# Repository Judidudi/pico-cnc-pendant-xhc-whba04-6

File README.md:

# Universal CNC Pendant

This repository contains the software and hardware for a complete CNC pendant that emulates the USB protocol of the original XHC WHB04B-6 pendant. It is designed to work with LinuxCNC, Beamicon2, Mach3 and Mach4 without any driver changes.

## Features

- **Drop-in WHB04B-6 emulation** – recognized by LinuxCNC's stock `xhc-whb04b-6` driver
- **60 mm handwheel**, rotary switches for axis selection and feed override
- **8 mechanical keys** (Kailh Choc V2) with configurable mapping
- **2.8" TFT touch display** (LVGL) showing machine position and status
- **Hardwired E-stop** – routed as a physical contact to the machine, completely independent of USB
- **Connection watchdog** – the pendant detects a lost host connection and can trigger the E-stop

## Compatibility

| Controller | Status |
|------------|--------|
| LinuxCNC   | To be tested |
| Beamicon2  | WIP |
| Mach3      | WIP |
| Mach4      | WIP |

## Repository structure

```
firmware/        Pico 2 W firmware (C, Pico SDK, TinyUSB, LVGL)
hardware/
  ├─ pcb/        KiCad projects (work in progress)
  ├─ enclosure/  Link to the printable parts on Printables
  └─ bom/        Bill of materials
docs/            Assembly guide, wiring, images
```

## Quickstart

1. Download the latest `.uf2` file from the [Releases](../../releases) page.
2. Hold the **BOOTSEL** button on the Pico while plugging in the USB cable. The Pico shows up as a USB drive.
3. Copy the `.uf2` file onto the drive. The Pico restarts automatically and the pendant is ready to use.

## Safety

- The **RESET** key toggles the machine on/off – it is **not** an emergency stop.
- The pendant's E-stop only protects you if it is wired into your machine's **hardware safety chain**. Never rely on a software-only E-stop.
- This is a hobby project. Build and use it at your own risk.

## To do

- Test and optimize the default button layout and add symbols to the keycaps
- Test with Beamicon2, Mach3 and Mach4
- Finish the hardware watchdog
- Design a custom PCB with an integrated RP2350 and all peripherals

## License

The original work in this repository is licensed under **TODO**, see [LICENSE](LICENSE).

Third-party components keep their own licenses:

| Component | License |
|-----------|---------|
| [LVGL](https://github.com/lvgl/lvgl) v8.3 | MIT |
| [TinyUSB](https://github.com/hathach/tinyusb) (via Pico SDK) | MIT |
| [Raspberry Pi Pico SDK](https://github.com/raspberrypi/pico-sdk) | BSD-3-Clause |

Full license texts: [THIRD_PARTY_LICENSES.md](THIRD_PARTY_LICENSES.md)

## Acknowledgements

- The LinuxCNC project and the authors of the `xhc-whb04b-6` component
- The LVGL and TinyUSB communities

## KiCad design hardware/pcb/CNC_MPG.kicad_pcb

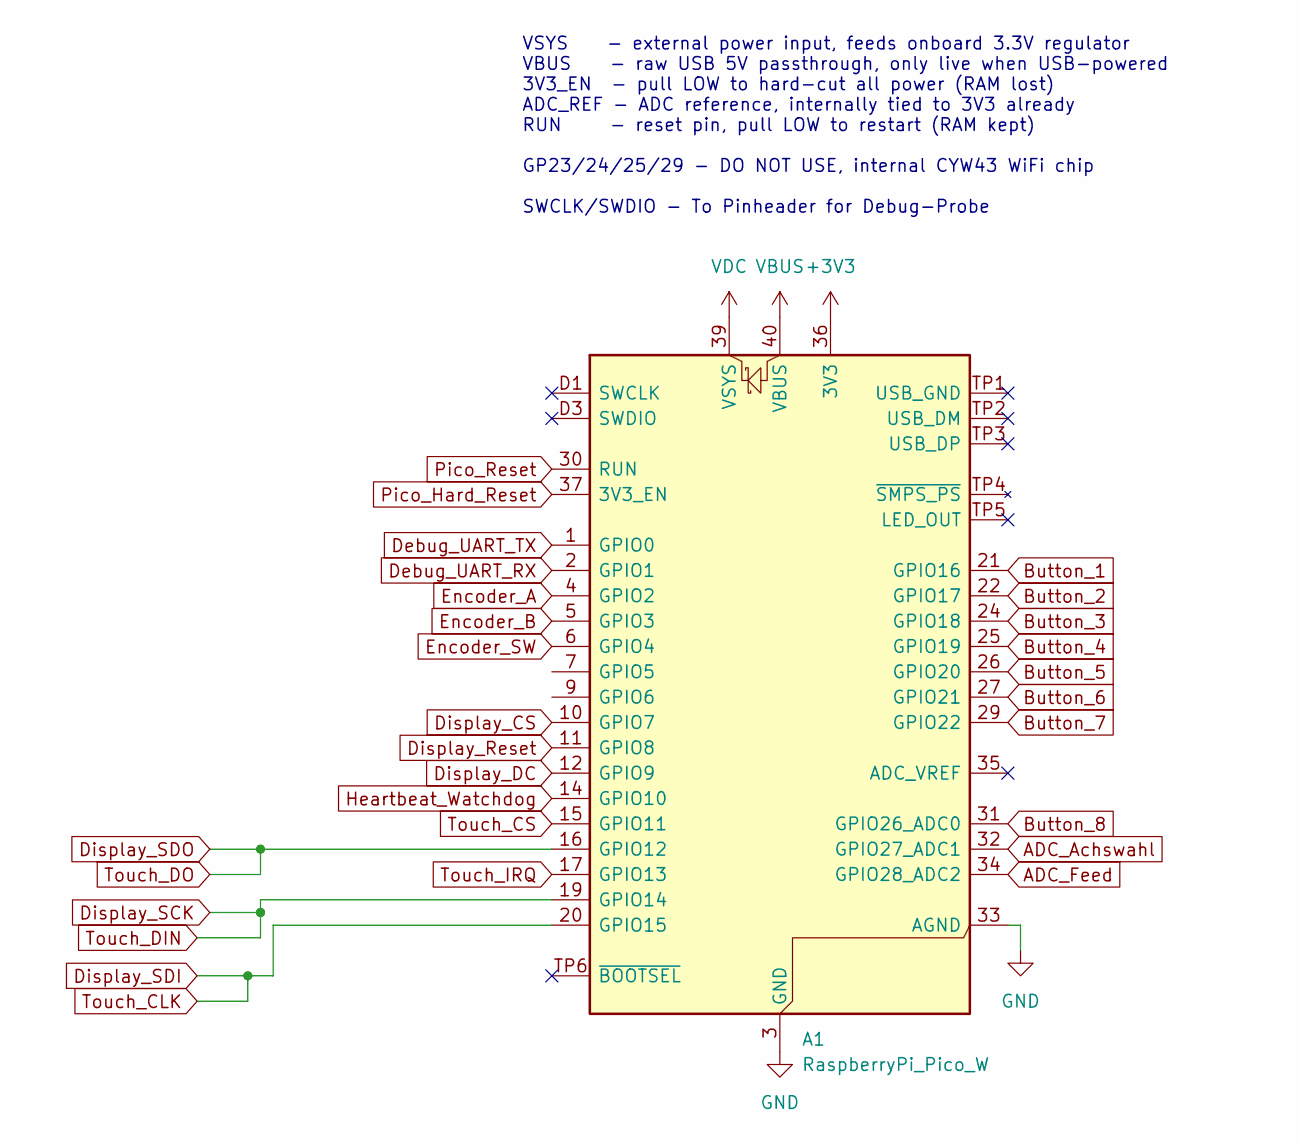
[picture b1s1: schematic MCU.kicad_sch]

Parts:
A1: RaspberryPi_Pico_W; RaspberryPi_Pico_Common_THT

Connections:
ADC_Achswahl: A1.32 (GPIO27_ADC1); also elsewhere on the board
ADC_Feed: A1.34 (GPIO28_ADC2); also elsewhere on the board
Button_1: A1.21 (GPIO16); also elsewhere on the board
Button_2: A1.22 (GPIO17); also elsewhere on the board
Button_3: A1.24 (GPIO18); also elsewhere on the board
Button_4: A1.25 (GPIO19); also elsewhere on the board
Button_5: A1.26 (GPIO20); also elsewhere on the board
Button_6: A1.27 (GPIO21); also elsewhere on the board
Button_7: A1.29 (GPIO22); also elsewhere on the board
Button_8: A1.31 (GPIO26_ADC0); also elsewhere on the board
Debug_UART_RX: A1.2 (GPIO1); also elsewhere on the board
Debug_UART_TX: A1.1 (GPIO0); also elsewhere on the board
Display_CS: A1.10 (GPIO7); also elsewhere on the board
Display_DC: A1.12 (GPIO9); also elsewhere on the board
Display_LED: A1.36 (3V3); also elsewhere on the board
Display_Reset: A1.11 (GPIO8); also elsewhere on the board
Display_SCK: A1.19 (GPIO14); also elsewhere on the board
Display_SDI: A1.20 (GPIO15); also elsewhere on the board
Display_SDO: A1.16 (GPIO12); also elsewhere on the board
Encoder_A: A1.4 (GPIO2); also elsewhere on the board
Encoder_B: A1.5 (GPIO3); also elsewhere on the board
Encoder_SW: A1.6 (GPIO4); also elsewhere on the board
GND: A1.3 (GND), A1.8 (GND), A1.13 (GND), A1.18 (GND), A1.23 (GND), A1.28 (GND), A1.33 (AGND), A1.38 (GND), A1.D2 (GND); also elsewhere on the board
Heartbeat_Watchdog: A1.14 (GPIO10)
Pico_Hard_Reset: A1.37 (3V3_EN)
Pico_Reset: A1.30 (RUN)
Touch_CS: A1.15 (GPIO11); also elsewhere on the board
Touch_IRQ: A1.17 (GPIO13); also elsewhere on the board
VBUS: A1.40 (VBUS)
VDC: A1.39 (VSYS)

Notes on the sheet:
VSYS - external power input, feeds onboard 3.3V regulator VBUS - raw USB 5V passthrough, only live when USB-powered 3V3_EN - pull LOW to hard-cut all power (RAM lost) ADC_REF - ADC reference, internally tied to 3V3 already RUN - reset pin, pull LOW to restart (RAM kept) GP23/24/25/29 - DO NOT USE, 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

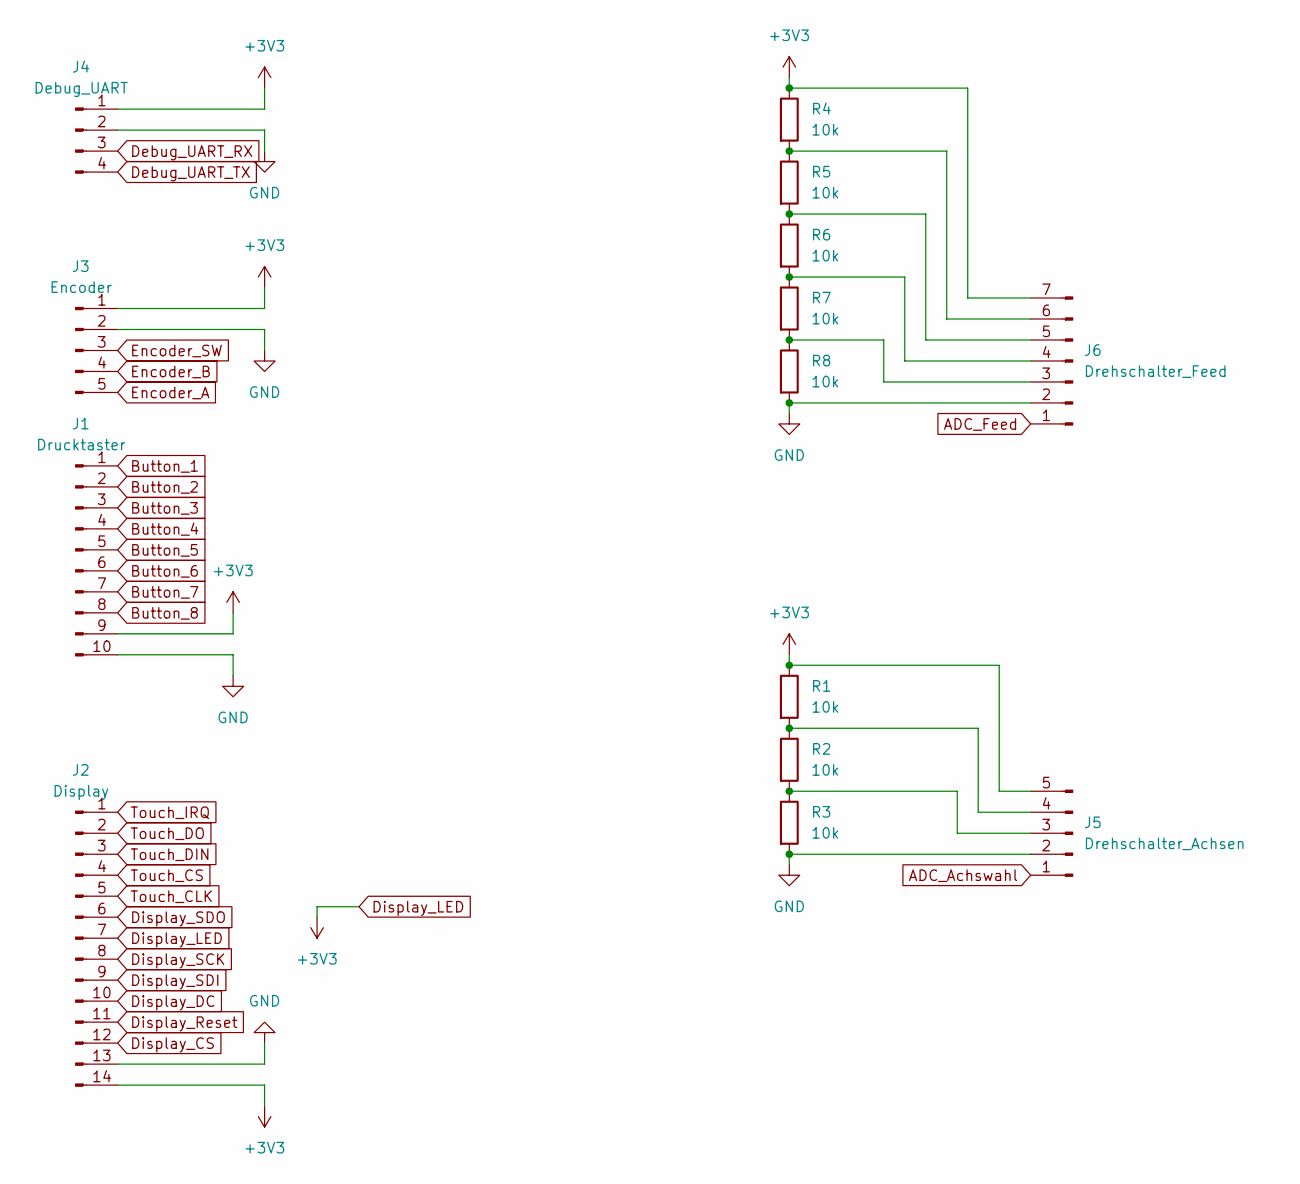
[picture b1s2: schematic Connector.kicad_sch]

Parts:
J1: Drucktaster; JST_PH_B10B-PH-K_1x10_P2.00mm_Vertical
J2: Display; JST_PH_B14B-PH-K_1x14_P2.00mm_Vertical
J3: Encoder; JST_PH_B5B-PH-K_1x05_P2.00mm_Vertical
J4: Debug_UART; PinHeader_1x04_P2.54mm_Vertical
J5: Drehschalter_Achsen; JST_PH_B5B-PH-K_1x05_P2.00mm_Vertical
J6: Drehschalter_Feed; JST_PH_B7B-PH-K_1x07_P2.00mm_Vertical
R1, R2, R3, R4, R5, R6, R7, R8: 10k; R_0603_1608Metric

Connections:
ADC_Achswahl: J5.1; also elsewhere on the board
ADC_Feed: J6.1; also elsewhere on the board
Button_1: J1.1; also elsewhere on the board
Button_2: J1.2; also elsewhere on the board
Button_3: J1.3; also elsewhere on the board
Button_4: J1.4; also elsewhere on the board
Button_5: J1.5; also elsewhere on the board
Button_6: J1.6; also elsewhere on the board
Button_7: J1.7; also elsewhere on the board
Button_8: J1.8; also elsewhere on the board
Debug_UART_RX: J4.3; also elsewhere on the board
Debug_UART_TX: J4.4; also elsewhere on the board
Display_CS: J2.12; also elsewhere on the board
Display_DC: J2.10; also elsewhere on the board
Display_LED: J1.9, J2.7, J2.14, J3.1, J4.1, J5.5, J6.7, R1.1, R4.1; also elsewhere on the board
Display_Reset: J2.11; also elsewhere on the board
Display_SCK: J2.3, J2.8; also elsewhere on the board
Display_SDI: J2.5, J2.9; also elsewhere on the board
Display_SDO: J2.2, J2.6; also elsewhere on the board
Encoder_A: J3.5; also elsewhere on the board
Encoder_B: J3.4; also elsewhere on the board
Encoder_SW: J3.3; also elsewhere on the board
GND: J1.10, J2.13, J3.2, J4.2, J5.2, J6.2, R3.2, R8.2; also elsewhere on the board
unnamed: J5.3, R2.2, R3.1
unnamed: J5.4, R1.2, R2.1
unnamed: J6.3, R7.2, R8.1
unnamed: J6.4, R6.2, R7.1
unnamed: J6.5, R5.2, R6.1
unnamed: J6.6, R4.2, R5.1
Touch_CS: J2.4; also elsewhere on the board
Touch_IRQ: J2.1; also elsewhere on the board

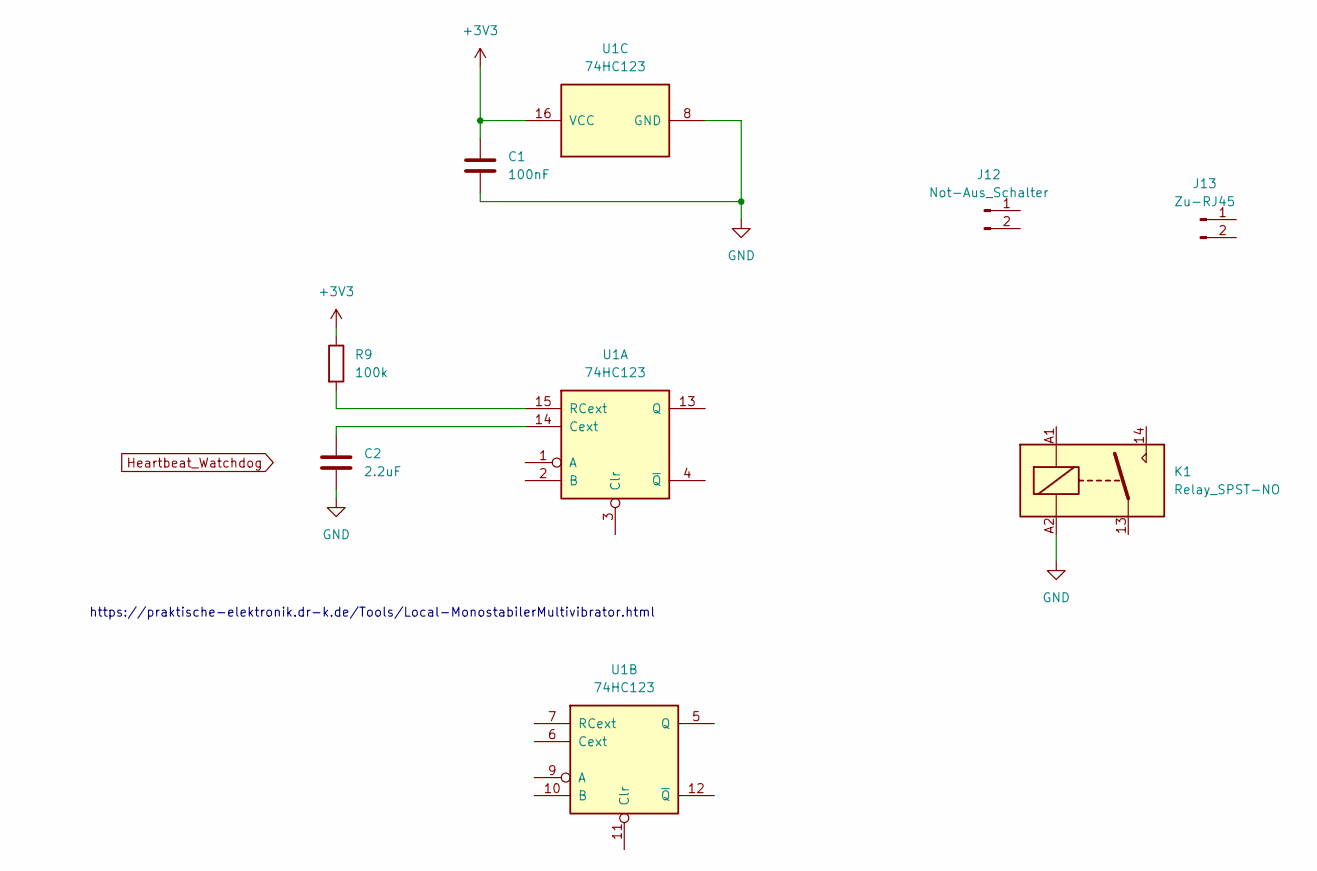
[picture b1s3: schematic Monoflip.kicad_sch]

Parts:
C1: 100nF; C_0603_1608Metric
C2: 2.2uF; C_0603_1608Metric
J12: Not-Aus_Schalter; JST_PH_B3B-PH-K_1x03_P2.00mm_Vertical
J13: Zu-RJ45; JST_PH_B3B-PH-K_1x03_P2.00mm_Vertical
K1: Relay_SPST-NO
R9: 100k; R_0603_1608Metric
U1: 74HC123

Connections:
Display_LED: C1.1, R9.1, U1.16 (VCC); also elsewhere on the board
GND: C1.2, C2.2, K1.A2, U1.8 (GND); also elsewhere on the board
unnamed: C2.1, U1.14 (Cext)
unnamed: R9.2, U1.15 (RCext)

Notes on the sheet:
https://praktische-elektronik.dr-k.de/Tools/Local-MonostabilerMultivibrator.html

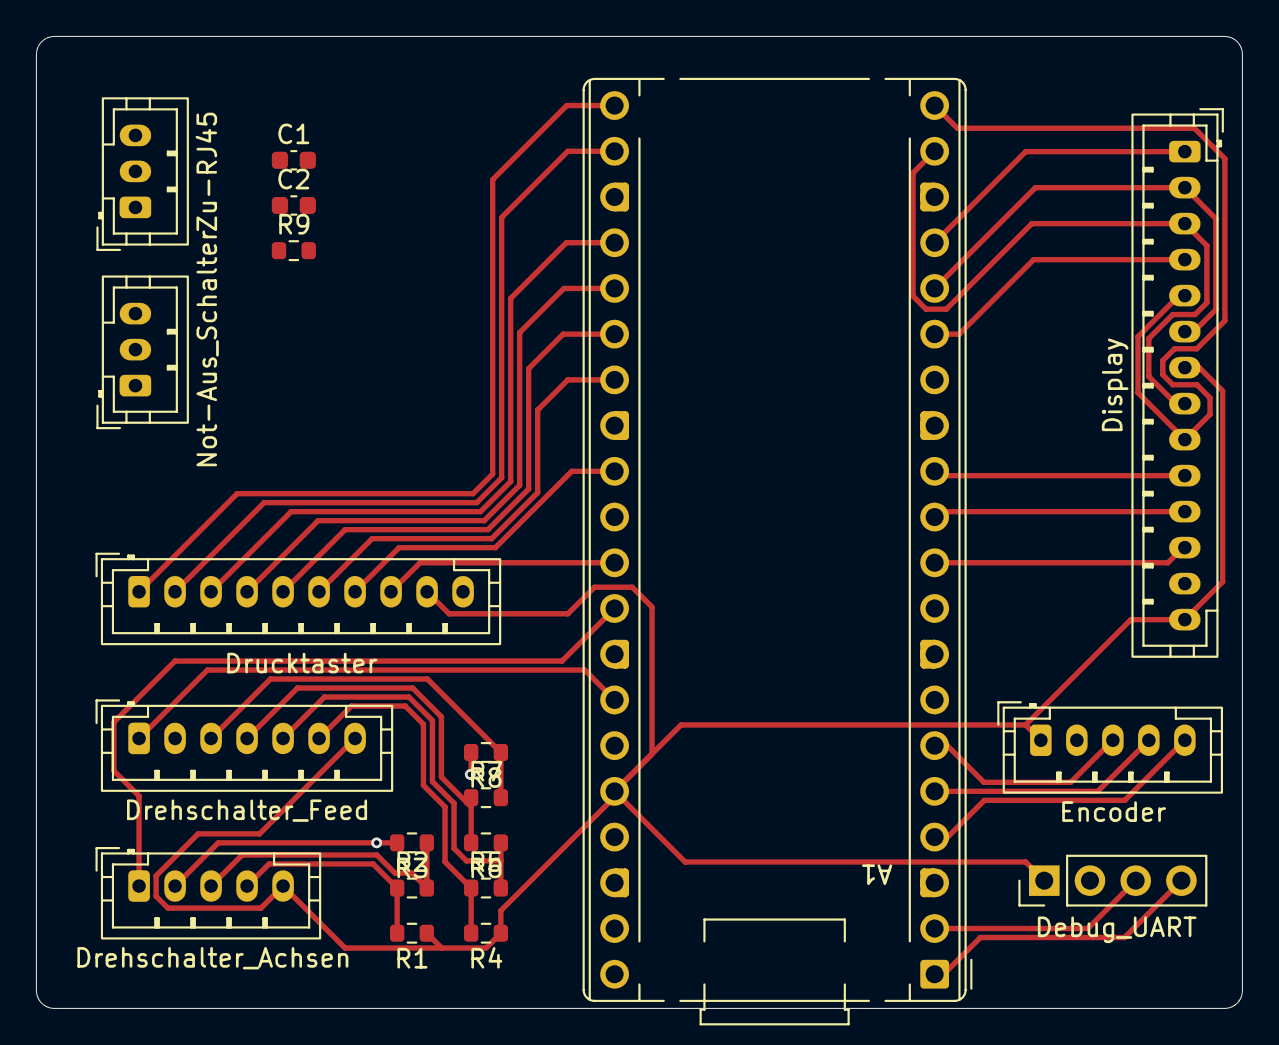
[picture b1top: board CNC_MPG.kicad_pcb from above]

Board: 2 copper layers, 67.0 x 54.0 mm, 20 parts (0 on the bottom side), 31 nets.

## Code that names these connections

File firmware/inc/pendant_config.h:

#ifndef PENDANT_CONFIG_H
#define PENDANT_CONFIG_H

// ---------------------------------------------------------------------
// Central pin and timing constants of the pendant.
// GP23/24/25/29 are used internally by the CYW43 WiFi chip on the Pico 2 W
// and must never appear here.
// ---------------------------------------------------------------------

// --- Encoder (hand wheel) ---
#define PIN_ENCODER_CLK 2
#define PIN_ENCODER_DT  3
#define PIN_ENCODER_SW  4  // push button inside the encoder knob

// Quadrature edges per mechanical detent. Typical detented encoders (a
// KY-040 for instance) run through one full cycle per detent and therefore
// deliver 4. Without this division one detent would trigger four jog steps.
#define ENCODER_COUNTS_PER_DETENT 4

// --- Function keys 1-8 ---
// Deliberately a list rather than a contiguous range: on the final PCB keys
// 1-7 sit on GP16-GP22 but key 8 sits on GP26, because GP23-GP25 belong to
// the CYW43 chip. Order equals key number 1 to 8.
#define PENDANT_BUTTON_PINS  { 16, 17, 18, 19, 20, 21, 22, 26 }
#define PENDANT_BUTTON_COUNT 8

// --- Safety heartbeat (retriggerable monostable on the board) ---
#define PIN_HEARTBEAT 10

// --- Display (ILI9341) + touch (XPT2046), shared SPI1 bus ---
// Only MISO/SCK/MOSI go through the SPI hardware. Both chip selects and the
// touch IRQ stay plain GPIOs: the driver switches chip select itself because
// two devices share one bus.
#define DISPLAY_SPI_INSTANCE spi1
#define PIN_DISPLAY_CS       7
#define PIN_DISPLAY_RESET    8
#define PIN_DISPLAY_DC       9
#define PIN_TOUCH_CS         11
#define PIN_DISPLAY_MISO     12  // SPI1 RX: display SDO + touch DO
#define PIN_TOUCH_IRQ        13  // plain input, NOT switched to the SPI function
#define PIN_DISPLAY_SCK      14  // SPI1 SCK
#define PIN_DISPLAY_MOSI     15  // SPI1 TX: display SDI + touch DIN

// SPI clock towards the display. 40 MHz is requested; the hardware divides
// the 150 MHz system clock and ends up at 37.5 MHz in practice.
//
// This value is the decisive lever for the loop time: a measurement at
// 7.5 MHz gave 20.30 ms per flush against 20.48 ms calculated (320 x 30
// pixels x 2 bytes = 153,600 bits). A flush is therefore 99 % waiting on the
// bus with no meaningful compute share. The ILI9341 is only specified for
// around 10 MHz but tolerates considerably more over short traces.
//
// On picture defects (noise, shifted lines, colour garbage) step back to
// 25 MHz. The XPT2046 on the same bus cannot follow this clock and switches
// itself to 2 MHz for its own measurement (see xpt2046_touch.c).
#define DISPLAY_SPI_BAUD_HZ (40 * 1000 * 1000)

// --- Rotary switches through a resistor ladder on the ADC ---
// GP26 would be ADC0 but serves as a digital input for key 8 on the final
// PCB - there is no third rotary switch here.
//
// Pin AND ADC index have to match: the ADC channels are fixed at GP26=ADC0,
// GP27=ADC1, GP28=ADC2. rotary_switch.c uses the pin for adc_gpio_init() and
// the index for adc_select_input() - if the two disagree, one pin is enabled
// as an analog input while a different one is measured. Nothing reports an
// error; the switch just shows nonsense.
#define PIN_ROTARY_AXIS       27  // ADC1, 4 positions (X/Y/Z/A)
#define PIN_ROTARY_FEED       28  // ADC2, 6 positions (step size / override)
#define ADC_INPUT_ROTARY_AXIS 1
#define ADC_INPUT_ROTARY_FEED 2

// --- Timing ---
#define BUTTON_DEBOUNCE_MS      20
#define WHB04B_REPORT_PERIOD_MS 2  // polling interval of the original pendant

// Toggle interval of the heartbeat. The time constant of the monostable has
// to be considerably larger (rule of thumb: >= 200 ms) so that a single long
// loop pass - a full-screen redraw over SPI, say - does not open the safety
// circuit on its own.
#define HEARTBEAT_INTERVAL_MS 50

// Beyond this long without display data the host software counts as silent.
// This is purely a DISPLAY warning and never triggers the safety circuit
// (reasoning in heartbeat.h).
#define HOST_DATA_TIMEOUT_MS 2000

#endif
